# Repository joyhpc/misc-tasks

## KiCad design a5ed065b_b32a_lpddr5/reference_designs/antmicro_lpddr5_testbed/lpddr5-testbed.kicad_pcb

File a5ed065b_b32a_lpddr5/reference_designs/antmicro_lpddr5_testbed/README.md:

# LPDDR5 Testbed

Copyright (c) 2023-2025 [Antmicro](https://www.antmicro.com)

## Overview

This project contains open hardware design files for an experimental test module in a mechanical form of SO-DIMM DDR5. 

The module includes a standard 315-ball WFBGA (12.4mm × 15.0mm × 0.8mm, Ø0.42 SMD) LPDDR5 RAM footprint break-routed in the SO-DIMM edge connector. 
The design files were prepared in KiCad 9.x. 

Please note that this board is not electrically compatible with off-the-shelf hot platforms accepting SO-DIMM DDR5 memory modules. 
It is compatible with [this](https://github.com/antmicro/sodimm-ddr5-tester) test platform.

## Project structure

The main project directory contains KiCad PCB project files, a LICENSE and README. 
The remaining files are stored in the following directories:

* `img` - contains graphics for this README
* `doc` - contains PDF schematic

## Licensing

This project is published under the [Apache-2.0](LICENSE) license.

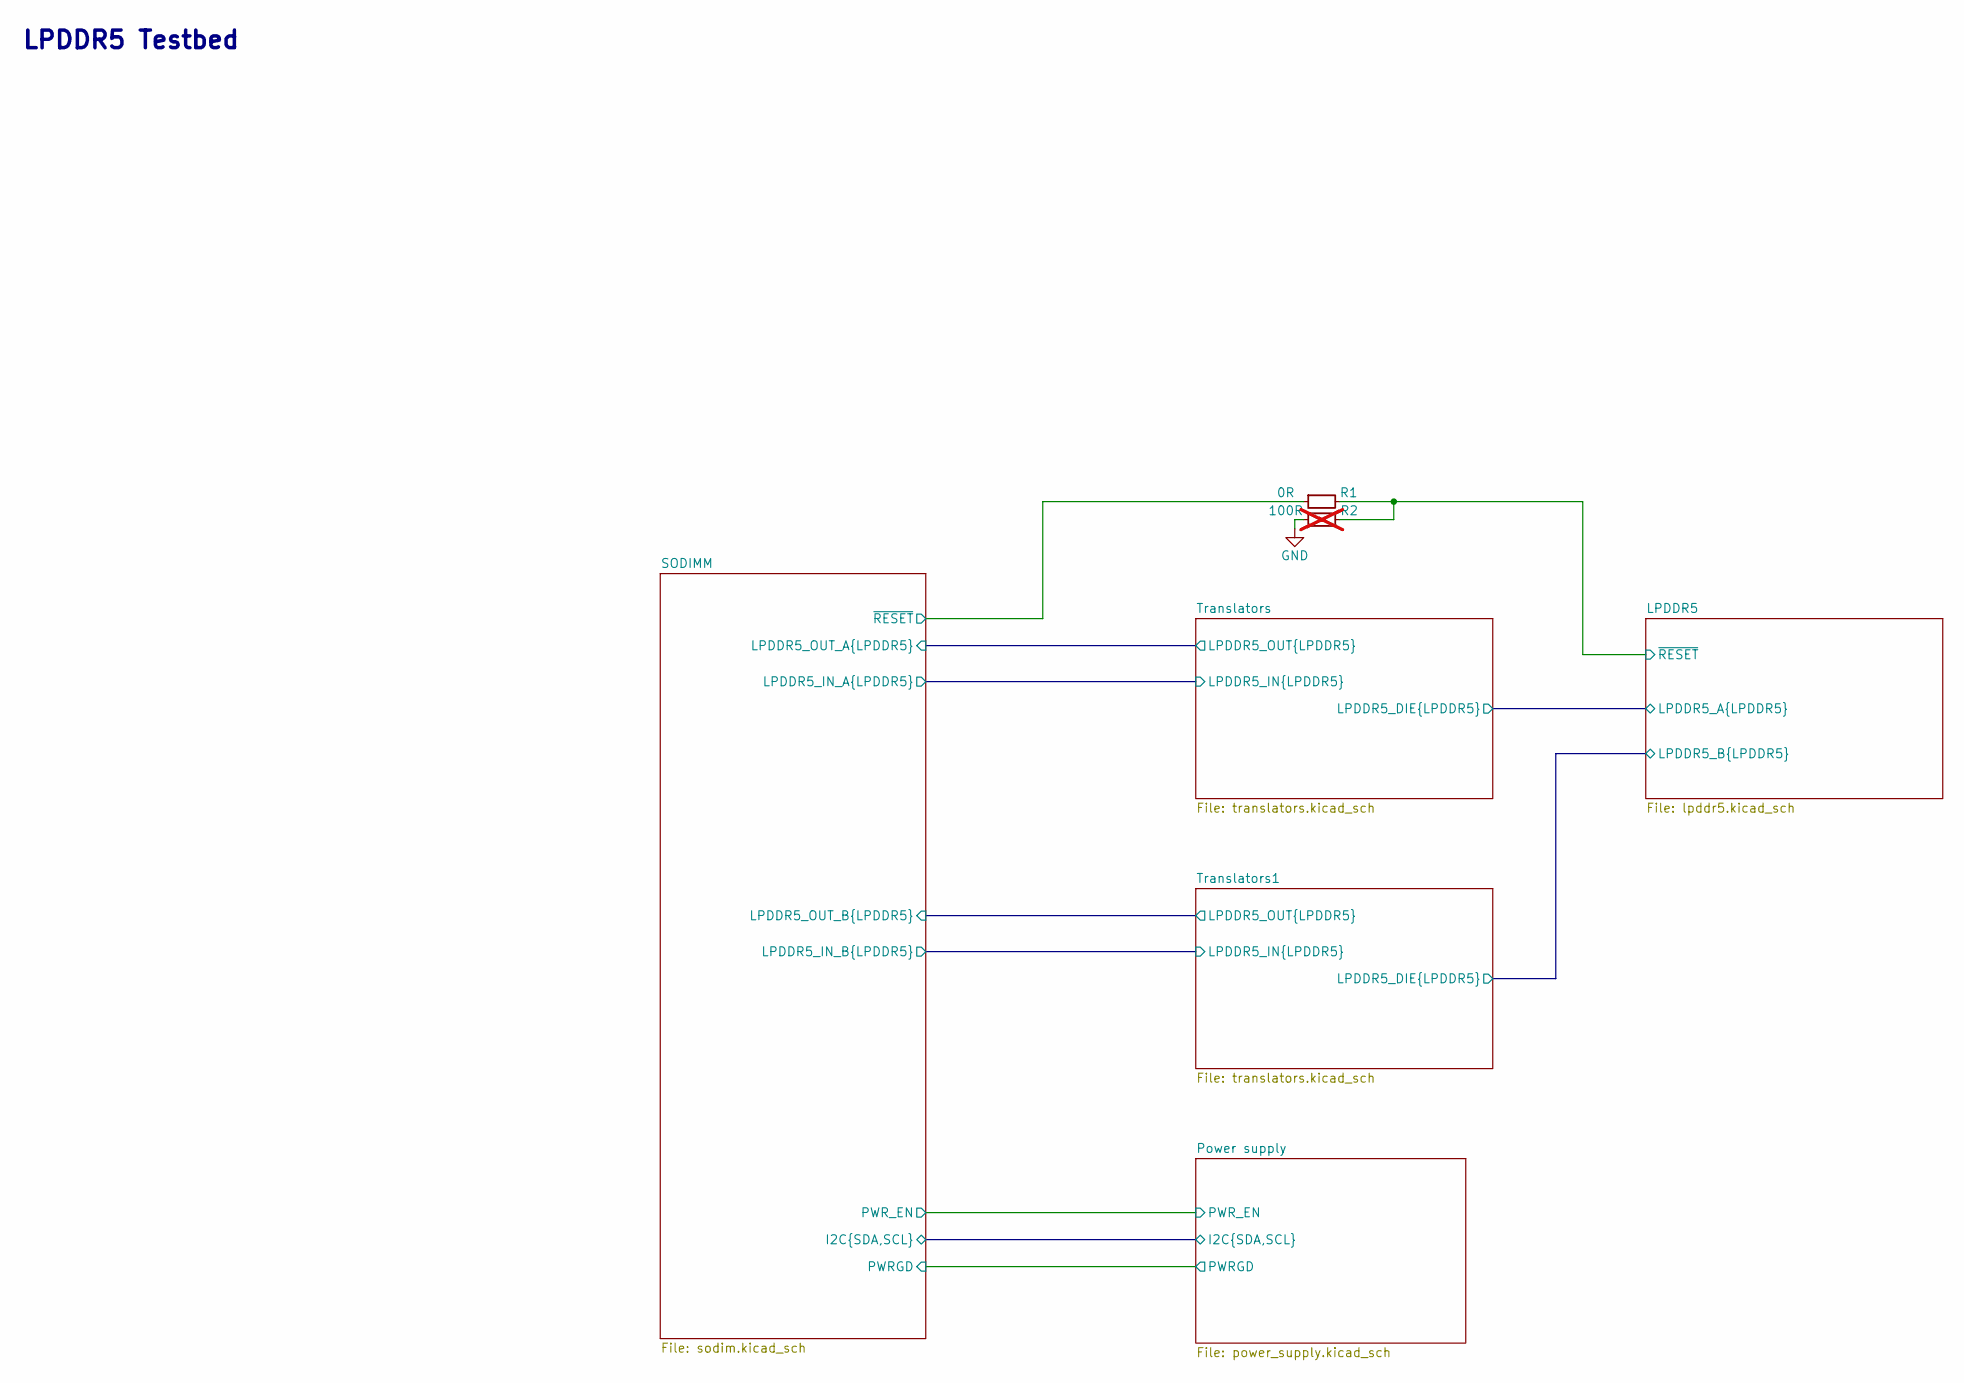
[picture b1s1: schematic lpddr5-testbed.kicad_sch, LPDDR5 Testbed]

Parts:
R1: R_0R_0402; R_0402_1005Metric; MPN ERJ2GE0R00X
R2: R_100R_0402; R_0402_1005Metric; Tolerance 1%; MPN CR0402-FX-1000GLF; not fitted

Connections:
/LPDDR5/~RESET: R1.2, R2.2; also elsewhere on the board
/SODIMM/~RESET: R1.1; also elsewhere on the board
GND: R2.1; also elsewhere on the board

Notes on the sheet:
LPDDR5 Testbed

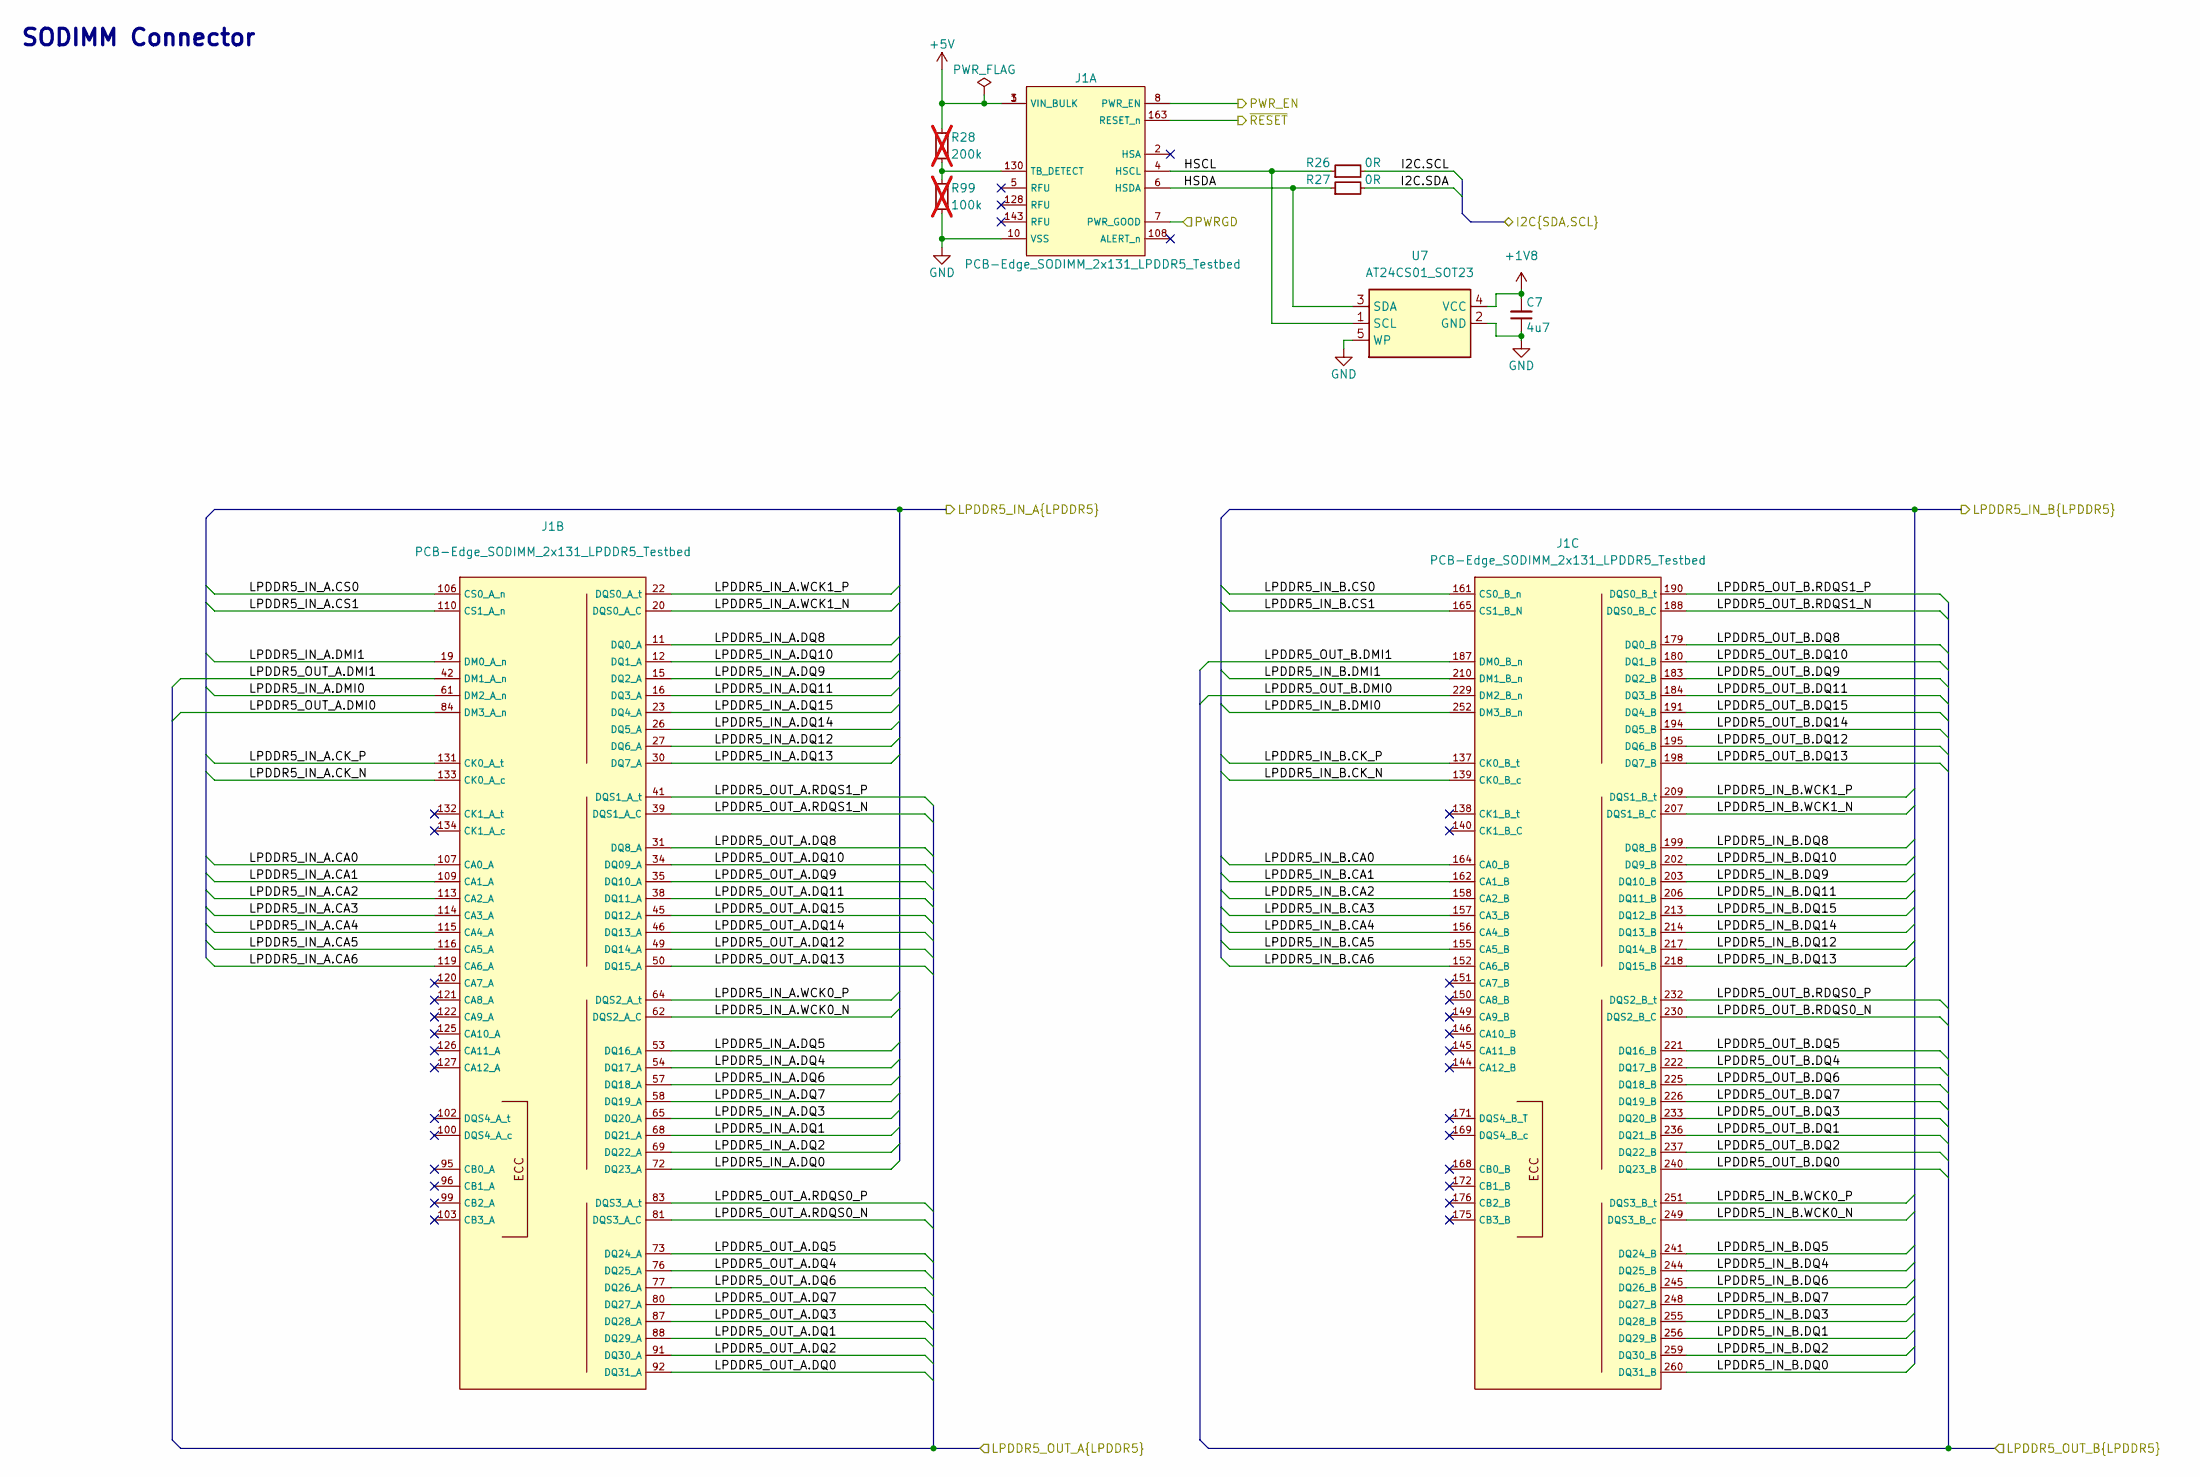
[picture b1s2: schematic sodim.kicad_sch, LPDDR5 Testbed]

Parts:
C7: C_4u7_0402; C_0402_1005Metric; MPN GRM155R61A475MEAAD
J1: PCB-Edge_SODIMM_2x131_LPDDR5_Testbed; Edge_Conn_Bus_DDR5_SODIMM
R26, R27: R_0R_0402; R_0402_1005Metric; MPN ERJ2GE0R00X
R28: R_200k_0402; R_0402_1005Metric; Tolerance 1%; MPN CR0402-FX-2003GLF; not fitted
R99: R_100k_0402; R_0402_1005Metric; Tolerance 1%; MPN CR0402-FX-1003GLF; not fitted
U7: AT24CS01_SOT23; SOT-23-5; MPN AT24CS01-ST

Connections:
+1V8: C7.2, U7.4 (VCC); also elsewhere on the board
+5V: J1.1 (VIN_BULK), J1.3 (VIN_BULK), R28.1; also elsewhere on the board
/LPDDR5/LPDDR5_A.DMI0: J1.84 (DM3_A_n); also elsewhere on the board
/LPDDR5/LPDDR5_A.DMI1: J1.42 (DM1_A_n); also elsewhere on the board
/LPDDR5/LPDDR5_A.DQ0: J1.92 (DQ31_A); also elsewhere on the board
/LPDDR5/LPDDR5_A.DQ1: J1.88 (DQ29_A); also elsewhere on the board
/LPDDR5/LPDDR5_A.DQ2: J1.91 (DQ30_A); also elsewhere on the board
/LPDDR5/LPDDR5_A.DQ3: J1.87 (DQ28_A); also elsewhere on the board
/LPDDR5/LPDDR5_A.DQ4: J1.76 (DQ25_A); also elsewhere on the board
/LPDDR5/LPDDR5_A.DQ5: J1.73 (DQ24_A); also elsewhere on the board
/LPDDR5/LPDDR5_A.DQ6: J1.77 (DQ26_A); also elsewhere on the board
/LPDDR5/LPDDR5_A.DQ7: J1.80 (DQ27_A); also elsewhere on the board
/LPDDR5/LPDDR5_A.DQ8: J1.31 (DQ8_A); also elsewhere on the board
/LPDDR5/LPDDR5_A.DQ9: J1.35 (DQ10_A); also elsewhere on the board
/LPDDR5/LPDDR5_A.DQ10: J1.34 (DQ09_A); also elsewhere on the board
/LPDDR5/LPDDR5_A.DQ11: J1.38 (DQ11_A); also elsewhere on the board
/LPDDR5/LPDDR5_A.DQ12: J1.49 (DQ14_A); also elsewhere on the board
/LPDDR5/LPDDR5_A.DQ13: J1.50 (DQ15_A); also elsewhere on the board
/LPDDR5/LPDDR5_A.DQ14: J1.46 (DQ13_A); also elsewhere on the board
/LPDDR5/LPDDR5_A.DQ15: J1.45 (DQ12_A); also elsewhere on the board
/LPDDR5/LPDDR5_A.RDQS0_N: J1.81 (DQS3_A_C); also elsewhere on the board
/LPDDR5/LPDDR5_A.RDQS0_P: J1.83 (DQS3_A_t); also elsewhere on the board
/LPDDR5/LPDDR5_A.RDQS1_N: J1.39 (DQS1_A_C); also elsewhere on the board
/LPDDR5/LPDDR5_A.RDQS1_P: J1.41 (DQS1_A_t); also elsewhere on the board
/LPDDR5/LPDDR5_B.DMI0: J1.229 (DM2_B_n); also elsewhere on the board
/LPDDR5/LPDDR5_B.DMI1: J1.187 (DM0_B_n); also elsewhere on the board
/LPDDR5/LPDDR5_B.DQ0: J1.240 (DQ23_B); also elsewhere on the board
/LPDDR5/LPDDR5_B.DQ1: J1.236 (DQ21_B); also elsewhere on the board
/LPDDR5/LPDDR5_B.DQ2: J1.237 (DQ22_B); also elsewhere on the board
/LPDDR5/LPDDR5_B.DQ3: J1.233 (DQ20_B); also elsewhere on the board
/LPDDR5/LPDDR5_B.DQ4: J1.222 (DQ17_B); also elsewhere on the board
/LPDDR5/LPDDR5_B.DQ5: J1.221 (DQ16_B); also elsewhere on the board
/LPDDR5/LPDDR5_B.DQ6: J1.225 (DQ18_B); also elsewhere on the board
/LPDDR5/LPDDR5_B.DQ7: J1.226 (DQ19_B); also elsewhere on the board
/LPDDR5/LPDDR5_B.DQ8: J1.179 (DQ0_B); also elsewhere on the board
/LPDDR5/LPDDR5_B.DQ9: J1.183 (DQ2_B); also elsewhere on the board
/LPDDR5/LPDDR5_B.DQ10: J1.180 (DQ1_B); also elsewhere on the board
/LPDDR5/LPDDR5_B.DQ11: J1.184 (DQ3_B); also elsewhere on the board
/LPDDR5/LPDDR5_B.DQ12: J1.195 (DQ6_B); also elsewhere on the board
/LPDDR5/LPDDR5_B.DQ13: J1.198 (DQ7_B); also elsewhere on the board
/LPDDR5/LPDDR5_B.DQ14: J1.194 (DQ5_B); also elsewhere on the board
/LPDDR5/LPDDR5_B.DQ15: J1.191 (DQ4_B); also elsewhere on the board
/LPDDR5/LPDDR5_B.RDQS0_N: J1.230 (DQS2_B_C); also elsewhere on the board
/LPDDR5/LPDDR5_B.RDQS0_P: J1.232 (DQS2_B_t); also elsewhere on the board
/LPDDR5/LPDDR5_B.RDQS1_N: J1.188 (DQS0_B_C); also elsewhere on the board
/LPDDR5/LPDDR5_B.RDQS1_P: J1.190 (DQS0_B_t); also elsewhere on the board
/Power supply/I2C.SCL: R26.2; also elsewhere on the board
/Power supply/I2C.SDA: R27.2; also elsewhere on the board
/Power supply/PWRGD: J1.7 (PWR_GOOD); also elsewhere on the board
/Power supply/PWR_EN: J1.8 (PWR_EN); also elsewhere on the board
/SODIMM/HSCL: J1.4 (HSCL), R26.1, U7.1 (SCL)
/SODIMM/HSDA: J1.6 (HSDA), R27.1, U7.3 (SDA)
/SODIMM/LPDDR5_IN_A.CA0: J1.107 (CA0_A); also elsewhere on the board
/SODIMM/LPDDR5_IN_A.CA1: J1.109 (CA1_A); also elsewhere on the board
/SODIMM/LPDDR5_IN_A.CA2: J1.113 (CA2_A); also elsewhere on the board
/SODIMM/LPDDR5_IN_A.CA3: J1.114 (CA3_A); also elsewhere on the board
/SODIMM/LPDDR5_IN_A.CA4: J1.115 (CA4_A); also elsewhere on the board
/SODIMM/LPDDR5_IN_A.CA5: J1.116 (CA5_A); also elsewhere on the board
/SODIMM/LPDDR5_IN_A.CA6: J1.119 (CA6_A); also elsewhere on the board
/SODIMM/LPDDR5_IN_A.CK_N: J1.133 (CK0_A_c); also elsewhere on the board
/SODIMM/LPDDR5_IN_A.CK_P: J1.131 (CK0_A_t); also elsewhere on the board
/SODIMM/LPDDR5_IN_A.CS0: J1.106 (CS0_A_n); also elsewhere on the board
/SODIMM/LPDDR5_IN_A.CS1: J1.110 (CS1_A_n); also elsewhere on the board
/SODIMM/LPDDR5_IN_A.DMI0: J1.61 (DM2_A_n); also elsewhere on the board
/SODIMM/LPDDR5_IN_A.DMI1: J1.19 (DM0_A_n); also elsewhere on the board
/SODIMM/LPDDR5_IN_A.DQ0: J1.72 (DQ23_A); also elsewhere on the board
/SODIMM/LPDDR5_IN_A.DQ1: J1.68 (DQ21_A); also elsewhere on the board
/SODIMM/LPDDR5_IN_A.DQ2: J1.69 (DQ22_A); also elsewhere on the board
/SODIMM/LPDDR5_IN_A.DQ3: J1.65 (DQ20_A); also elsewhere on the board
/SODIMM/LPDDR5_IN_A.DQ4: J1.54 (DQ17_A); also elsewhere on the board
/SODIMM/LPDDR5_IN_A.DQ5: J1.53 (DQ16_A); also elsewhere on the board
/SODIMM/LPDDR5_IN_A.DQ6: J1.57 (DQ18_A); also elsewhere on the board
/SODIMM/LPDDR5_IN_A.DQ7: J1.58 (DQ19_A); also elsewhere on the board
/SODIMM/LPDDR5_IN_A.DQ8: J1.11 (DQ0_A); also elsewhere on the board
/SODIMM/LPDDR5_IN_A.DQ9: J1.15 (DQ2_A); also elsewhere on the board
/SODIMM/LPDDR5_IN_A.DQ10: J1.12 (DQ1_A); also elsewhere on the board
/SODIMM/LPDDR5_IN_A.DQ11: J1.16 (DQ3_A); also elsewhere on the board
/SODIMM/LPDDR5_IN_A.DQ12: J1.27 (DQ6_A); also elsewhere on the board
/SODIMM/LPDDR5_IN_A.DQ13: J1.30 (DQ7_A); also elsewhere on the board
/SODIMM/LPDDR5_IN_A.DQ14: J1.26 (DQ5_A); also elsewhere on the board
/SODIMM/LPDDR5_IN_A.DQ15: J1.23 (DQ4_A); also elsewhere on the board
/SODIMM/LPDDR5_IN_A.WCK0_N: J1.62 (DQS2_A_C); also elsewhere on the board
/SODIMM/LPDDR5_IN_A.WCK0_P: J1.64 (DQS2_A_t); also elsewhere on the board
/SODIMM/LPDDR5_IN_A.WCK1_N: J1.20 (DQS0_A_C); also elsewhere on the board
/SODIMM/LPDDR5_IN_A.WCK1_P: J1.22 (DQS0_A_t); also elsewhere on the board
/SODIMM/LPDDR5_IN_B.CA0: J1.164 (CA0_B); also elsewhere on the board
/SODIMM/LPDDR5_IN_B.CA1: J1.162 (CA1_B); also elsewhere on the board
/SODIMM/LPDDR5_IN_B.CA2: J1.158 (CA2_B); also elsewhere on the board
/SODIMM/LPDDR5_IN_B.CA3: J1.157 (CA3_B); also elsewhere on the board
/SODIMM/LPDDR5_IN_B.CA4: J1.156 (CA4_B); also elsewhere on the board
/SODIMM/LPDDR5_IN_B.CA5: J1.155 (CA5_B); also elsewhere on the board
/SODIMM/LPDDR5_IN_B.CA6: J1.152 (CA6_B); also elsewhere on the board
/SODIMM/LPDDR5_IN_B.CK_N: J1.139 (CK0_B_c); also elsewhere on the board
/SODIMM/LPDDR5_IN_B.CK_P: J1.137 (CK0_B_t); also elsewhere on the board
/SODIMM/LPDDR5_IN_B.CS0: J1.161 (CS0_B_n); also elsewhere on the board
/SODIMM/LPDDR5_IN_B.CS1: J1.165 (CS1_B_N); also elsewhere on the board
/SODIMM/LPDDR5_IN_B.DMI0: J1.252 (DM3_B_n); also elsewhere on the board
/SODIMM/LPDDR5_IN_B.DMI1: J1.210 (DM1_B_n); also elsewhere on the board
/SODIMM/LPDDR5_IN_B.DQ0: J1.260 (DQ31_B); also elsewhere on the board
/SODIMM/LPDDR5_IN_B.DQ1: J1.256 (DQ29_B); also elsewhere on the board
/SODIMM/LPDDR5_IN_B.DQ2: J1.259 (DQ30_B); also elsewhere on the board
/SODIMM/LPDDR5_IN_B.DQ3: J1.255 (DQ28_B); also elsewhere on the board
/SODIMM/LPDDR5_IN_B.DQ4: J1.244 (DQ25_B); also elsewhere on the board
/SODIMM/LPDDR5_IN_B.DQ5: J1.241 (DQ24_B); also elsewhere on the board
/SODIMM/LPDDR5_IN_B.DQ6: J1.245 (DQ26_B); also elsewhere on the board
/SODIMM/LPDDR5_IN_B.DQ7: J1.248 (DQ27_B); also elsewhere on the board
/SODIMM/LPDDR5_IN_B.DQ8: J1.199 (DQ8_B); also elsewhere on the board
/SODIMM/LPDDR5_IN_B.DQ9: J1.203 (DQ10_B); also elsewhere on the board
/SODIMM/LPDDR5_IN_B.DQ10: J1.202 (DQ9_B); also elsewhere on the board
/SODIMM/LPDDR5_IN_B.DQ11: J1.206 (DQ11_B); also elsewhere on the board
/SODIMM/LPDDR5_IN_B.DQ12: J1.217 (DQ14_B); also elsewhere on the board
/SODIMM/LPDDR5_IN_B.DQ13: J1.218 (DQ15_B); also elsewhere on the board
/SODIMM/LPDDR5_IN_B.DQ14: J1.214 (DQ13_B); also elsewhere on the board
/SODIMM/LPDDR5_IN_B.DQ15: J1.213 (DQ12_B); also elsewhere on the board
/SODIMM/LPDDR5_IN_B.WCK0_N: J1.249 (DQS3_B_c); also elsewhere on the board
/SODIMM/LPDDR5_IN_B.WCK0_P: J1.251 (DQS3_B_t); also elsewhere on the board
/SODIMM/LPDDR5_IN_B.WCK1_N: J1.207 (DQS1_B_C); also elsewhere on the board
/SODIMM/LPDDR5_IN_B.WCK1_P: J1.209 (DQS1_B_t); also elsewhere on the board
/SODIMM/~RESET: J1.163 (RESET_n); also elsewhere on the board
GND: C7.1, J1.9 (VSS), J1.10 (VSS), J1.13 (VSS), J1.14 (VSS), J1.17 (VSS), J1.18 (VSS), J1.21 (VSS), J1.24 (VSS), J1.25 (VSS), J1.28 (VSS), J1.29 (VSS), J1.32 (VSS), J1.33 (VSS), J1.36 (VSS), J1.37 (VSS), J1.40 (VSS), J1.43 (VSS), J1.44 (VSS), J1.47 (VSS), J1.48 (VSS), J1.51 (VSS), J1.52 (VSS), J1.55 (VSS), J1.56 (VSS), J1.59 (VSS), J1.60 (VSS), J1.63 (VSS), J1.66 (VSS), J1.67 (VSS), J1.70 (VSS), J1.71 (VSS), J1.74 (VSS), J1.75 (VSS), J1.78 (VSS), J1.79 (VSS), J1.82 (VSS), J1.85 (VSS), J1.86 (VSS), J1.89 (VSS), J1.90 (VSS), J1.93 (VSS), J1.94 (VSS), J1.97 (VSS), J1.98 (VSS), J1.101 (VSS), J1.104 (VSS), J1.105 (VSS), J1.111 (VSS), J1.112 (VSS), J1.117 (VSS), J1.118 (VSS), J1.123 (VSS), J1.124 (VSS), J1.129 (VSS), J1.135 (VSS), J1.136 (VSS), J1.141 (VSS), J1.142 (VSS), J1.147 (VSS), J1.148 (VSS), J1.153 (VSS), J1.154 (VSS), J1.159 (VSS), J1.160 (VSS), J1.166 (VSS), J1.167 (VSS), J1.170 (VSS), J1.173 (VSS), J1.174 (VSS), J1.177 (VSS), J1.178 (VSS), J1.181 (VSS), J1.182 (VSS), J1.185 (VSS), J1.186 (VSS), J1.189 (VSS), J1.192 (VSS), J1.193 (VSS), J1.196 (VSS), J1.197 (VSS), J1.200 (VSS), J1.201 (VSS), J1.204 (VSS), J1.205 (VSS), J1.208 (VSS), J1.211 (VSS), J1.212 (VSS), J1.215 (VSS), J1.216 (VSS), J1.219 (VSS), J1.220 (VSS), J1.223 (VSS), J1.224 (VSS), J1.227 (VSS), J1.228 (VSS), J1.231 (VSS), J1.234 (VSS), J1.235 (VSS), J1.238 (VSS), J1.239 (VSS), J1.242 (VSS), J1.243 (VSS), J1.246 (VSS), J1.247 (VSS), J1.250 (VSS), J1.253 (VSS), J1.254 (VSS), J1.257 (VSS), J1.258 (VSS), J1.261 (VSS), J1.262 (VSS), R99.2, U7.2 (GND), U7.5 (WP); also elsewhere on the board
unnamed: J1.130 (TB_DETECT), R28.2, R99.1

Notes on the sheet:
SODIMM Connector

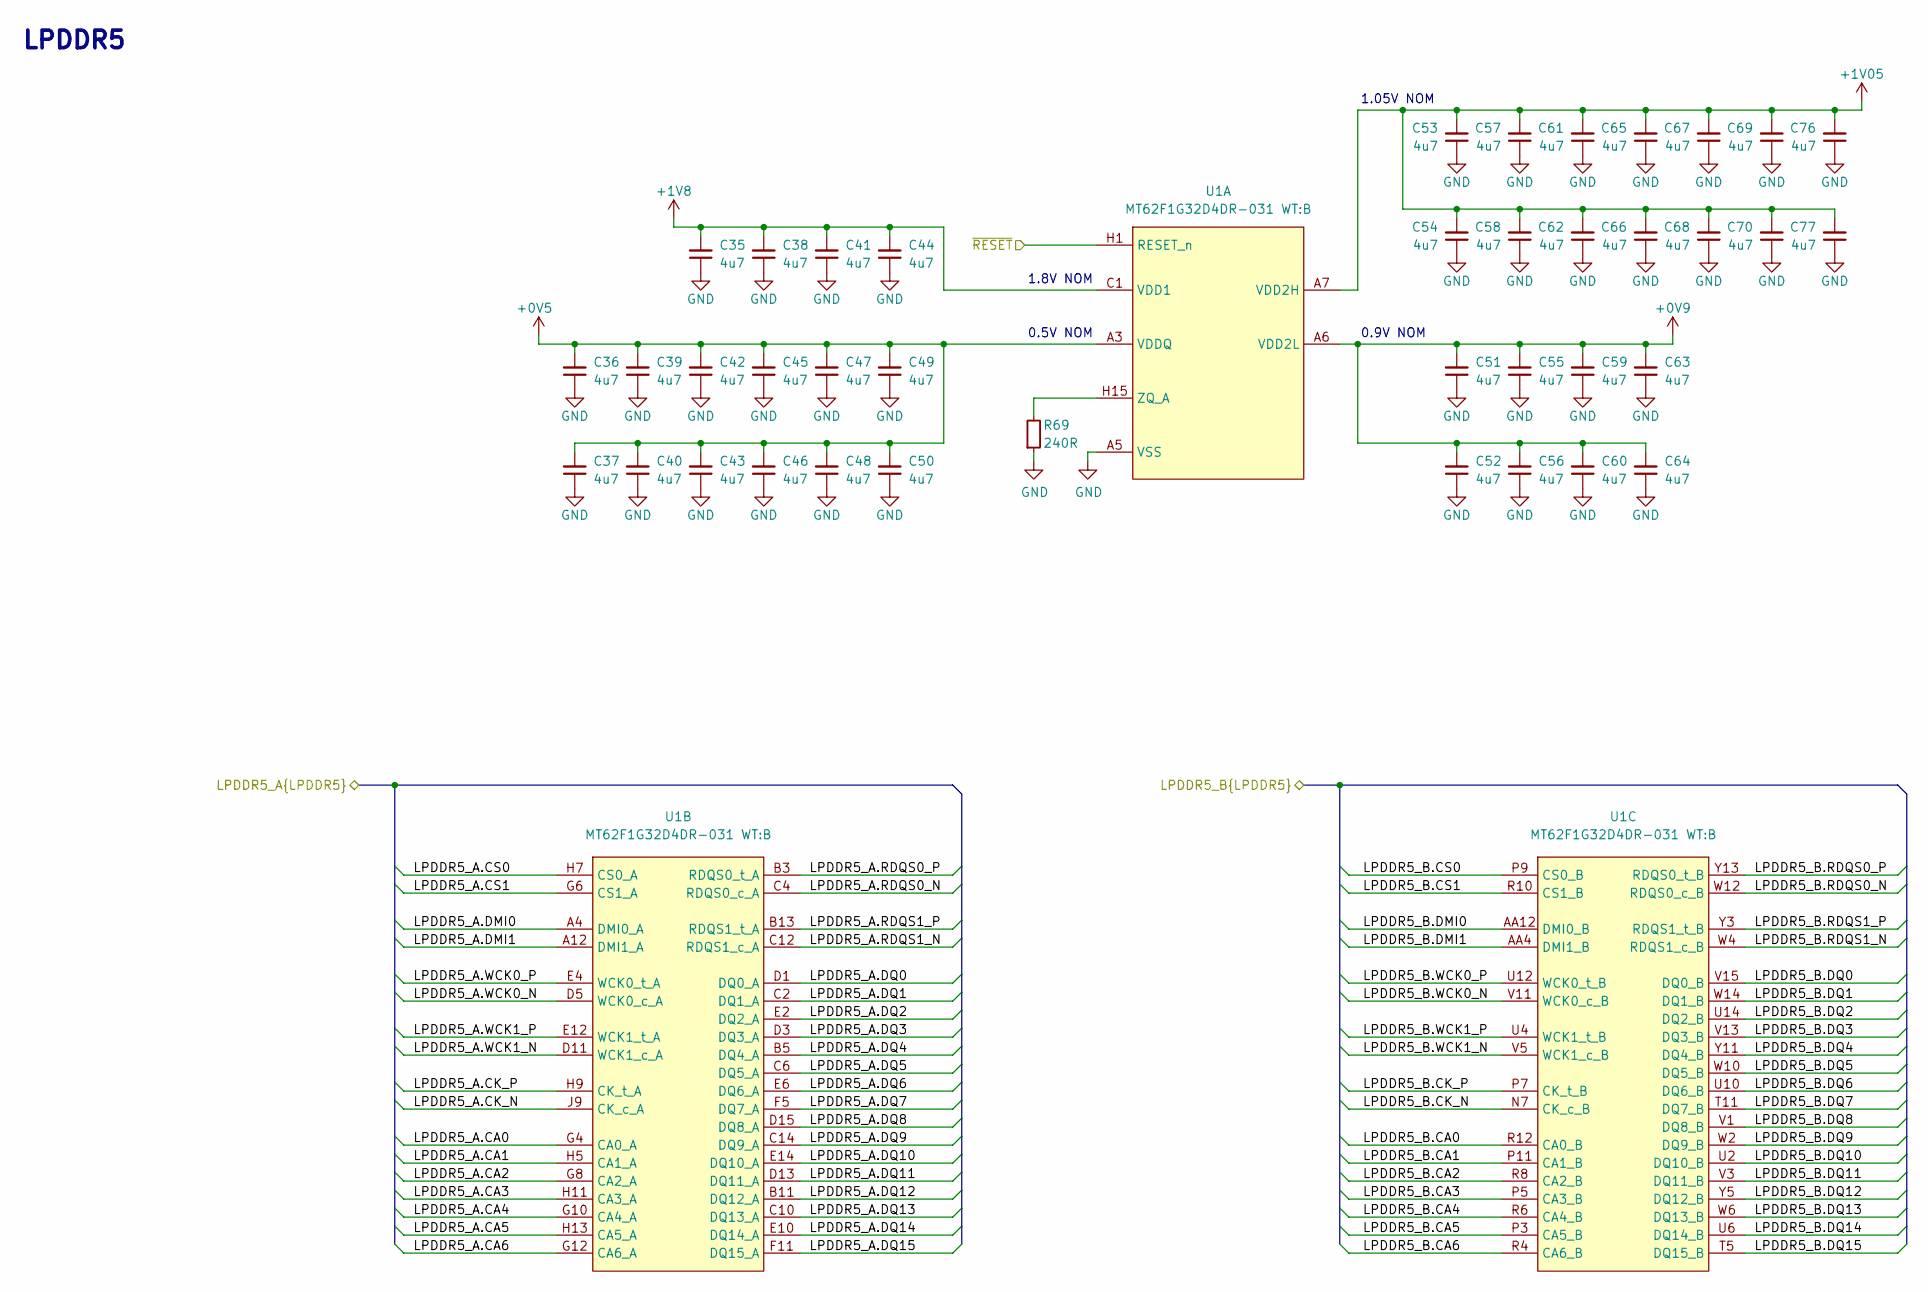
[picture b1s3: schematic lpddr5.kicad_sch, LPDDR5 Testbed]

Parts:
C35, C36, C37, C38, C39, C40, C41, C42, C43, C44, C45, C46, C47, C48, C49, C50, C51, C52, C53, C54, C55, C56, C57, C58, C59, C60, C61, C62, C63, C64, C65, C66, C67, C68, C69, C70, C76, C77: C_4u7_0402; C_0402_1005Metric; MPN GRM155R61A475MEAAD
R69: R_240R_0402; R_0402_1005Metric; Tolerance 1%; MPN CR0402-FX-2400GLF
U1: MT62F1G32D4DR-031; BGA-315_12.4x15mm_Layout15x21_P0.8x0.7mm; MPN MT62F1G32D4DR-031 WT:B

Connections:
+0V5: C36.2, C37.2, C39.2, C40.2, C42.2, C43.2, C45.2, C46.2, C47.2, C48.2, C49.2, C50.2, U1.A3 (VDDQ), U1.A13 (VDDQ), U1.AA3 (VDDQ), U1.AA13 (VDDQ), U1.B2 (VDDQ), U1.B14 (VDDQ), U1.C3 (VDDQ), U1.C13 (VDDQ), U1.D4 (VDDQ), U1.D12 (VDDQ), U1.E5 (VDDQ), U1.E11 (VDDQ), U1.F1 (VDDQ), U1.F3 (VDDQ), U1.F4 (VDDQ), U1.F12 (VDDQ), U1.F13 (VDDQ), U1.F15 (VDDQ), U1.G1 (VDDQ), U1.G2 (VDDQ), U1.G14 (VDDQ), U1.G15 (VDDQ), U1.R1 (VDDQ), U1.R2 (VDDQ), U1.R14 (VDDQ), U1.R15 (VDDQ), U1.T1 (VDDQ), U1.T3 (VDDQ), U1.T4 (VDDQ), U1.T12 (VDDQ), U1.T13 (VDDQ), U1.T15 (VDDQ), U1.U5 (VDDQ), U1.U11 (VDDQ), U1.V4 (VDDQ), U1.V12 (VDDQ), U1.W3 (VDDQ), U1.W13 (VDDQ), U1.Y2 (VDDQ), U1.Y14 (VDDQ); also elsewhere on the board
+0V9: C51.2, C52.2, C55.2, C56.2, C59.2, C60.2, C63.2, C64.2, U1.A6 (VDD2L), U1.A10 (VDD2L), U1.AA6 (VDD2L), U1.AA10 (VDD2L), U1.B6 (VDD2L), U1.B10 (VDD2L), U1.H2 (VDD2L), U1.H14 (VDD2L), U1.J2 (VDD2L), U1.J14 (VDD2L), U1.N2 (VDD2L), U1.N14 (VDD2L), U1.P2 (VDD2L), U1.P14 (VDD2L), U1.Y6 (VDD2L), U1.Y10 (VDD2L); also elsewhere on the board
+1V05: C53.2, C54.2, C57.2, C58.2, C61.2, C62.2, C65.2, C66.2, C67.2, C68.2, C69.2, C70.2, C76.2, C77.2, U1.A7 (VDD2H), U1.A8 (VDD2H), U1.A9 (VDD2H), U1.AA7 (VDD2H), U1.AA8 (VDD2H), U1.AA9 (VDD2H), U1.B7 (VDD2H), U1.B9 (VDD2H), U1.C7 (VDD2H), U1.C9 (VDD2H), U1.D8 (VDD2H), U1.E7 (VDD2H), U1.E9 (VDD2H), U1.F6 (VDD2H), U1.F7 (VDD2H), U1.F9 (VDD2H), U1.F10 (VDD2H), U1.J5 (VDD2H), U1.J11 (VDD2H), U1.K1 (VDD2H), U1.K2 (VDD2H), U1.K3 (VDD2H), U1.K4 (VDD2H), U1.K5 (VDD2H), U1.K6 (VDD2H), U1.K10 (VDD2H), U1.K11 (VDD2H), U1.K12 (VDD2H), U1.K13 (VDD2H), U1.K14 (VDD2H), U1.K15 (VDD2H), U1.L6 (VDD2H), U1.L7 (VDD2H), U1.L8 (VDD2H), U1.L9 (VDD2H), U1.L10 (VDD2H), U1.M1 (VDD2H), U1.M2 (VDD2H), U1.M3 (VDD2H), U1.M4 (VDD2H), U1.M5 (VDD2H), U1.M6 (VDD2H), U1.M10 (VDD2H), U1.M11 (VDD2H), U1.M12 (VDD2H), U1.M13 (VDD2H), U1.M14 (VDD2H), U1.M15 (VDD2H), U1.N5 (VDD2H), U1.N11 (VDD2H), U1.T6 (VDD2H), U1.T7 (VDD2H), U1.T9 (VDD2H), U1.T10 (VDD2H), U1.U7 (VDD2H), U1.U9 (VDD2H), U1.V8 (VDD2H), U1.W7 (VDD2H), U1.W9 (VDD2H), U1.Y7 (VDD2H), U1.Y9 (VDD2H); also elsewhere on the board
+1V8: C35.2, C38.2, C41.2, C44.2, U1.C1 (VDD1), U1.C15 (VDD1), U1.W1 (VDD1), U1.W15 (VDD1); also elsewhere on the board
/LPDDR5/LPDDR5_A.CA0: U1.G4 (CA0_A); also elsewhere on the board
/LPDDR5/LPDDR5_A.CA1: U1.H5 (CA1_A); also elsewhere on the board
/LPDDR5/LPDDR5_A.CA2: U1.G8 (CA2_A); also elsewhere on the board
/LPDDR5/LPDDR5_A.CA3: U1.H11 (CA3_A); also elsewhere on the board
/LPDDR5/LPDDR5_A.CA4: U1.G10 (CA4_A); also elsewhere on the board
/LPDDR5/LPDDR5_A.CA5: U1.H13 (CA5_A); also elsewhere on the board
/LPDDR5/LPDDR5_A.CA6: U1.G12 (CA6_A); also elsewhere on the board
/LPDDR5/LPDDR5_A.CK_N: U1.J9 (CK_c_A); also elsewhere on the board
/LPDDR5/LPDDR5_A.CK_P: U1.H9 (CK_t_A); also elsewhere on the board
/LPDDR5/LPDDR5_A.CS0: U1.H7 (CS0_A); also elsewhere on the board
/LPDDR5/LPDDR5_A.CS1: U1.G6 (CS1_A); also elsewhere on the board
/LPDDR5/LPDDR5_A.DMI0: U1.A4 (DMI0_A); also elsewhere on the board
/LPDDR5/LPDDR5_A.DMI1: U1.A12 (DMI1_A); also elsewhere on the board
/LPDDR5/LPDDR5_A.DQ0: U1.D1 (DQ0_A); also elsewhere on the board
/LPDDR5/LPDDR5_A.DQ1: U1.C2 (DQ1_A); also elsewhere on the board
/LPDDR5/LPDDR5_A.DQ2: U1.E2 (DQ2_A); also elsewhere on the board
/LPDDR5/LPDDR5_A.DQ3: U1.D3 (DQ3_A); also elsewhere on the board
/LPDDR5/LPDDR5_A.DQ4: U1.B5 (DQ4_A); also elsewhere on the board
/LPDDR5/LPDDR5_A.DQ5: U1.C6 (DQ5_A); also elsewhere on the board
/LPDDR5/LPDDR5_A.DQ6: U1.E6 (DQ6_A); also elsewhere on the board
/LPDDR5/LPDDR5_A.DQ7: U1.F5 (DQ7_A); also elsewhere on the board
/LPDDR5/LPDDR5_A.DQ8: U1.D15 (DQ8_A); also elsewhere on the board
/LPDDR5/LPDDR5_A.DQ9: U1.C14 (DQ9_A); also elsewhere on the board
/LPDDR5/LPDDR5_A.DQ10: U1.E14 (DQ10_A); also elsewhere on the board
/LPDDR5/LPDDR5_A.DQ11: U1.D13 (DQ11_A); also elsewhere on the board
/LPDDR5/LPDDR5_A.DQ12: U1.B11 (DQ12_A); also elsewhere on the board
/LPDDR5/LPDDR5_A.DQ13: U1.C10 (DQ13_A); also elsewhere on the board
/LPDDR5/LPDDR5_A.DQ14: U1.E10 (DQ14_A); also elsewhere on the board
/LPDDR5/LPDDR5_A.DQ15: U1.F11 (DQ15_A); also elsewhere on the board
/LPDDR5/LPDDR5_A.RDQS0_N: U1.C4 (RDQS0_c_A); also elsewhere on the board
/LPDDR5/LPDDR5_A.RDQS0_P: U1.B3 (RDQS0_t_A); also elsewhere on the board
/LPDDR5/LPDDR5_A.RDQS1_N: U1.C12 (RDQS1_c_A); also elsewhere on the board
/LPDDR5/LPDDR5_A.RDQS1_P: U1.B13 (RDQS1_t_A); also elsewhere on the board
/LPDDR5/LPDDR5_A.WCK0_N: U1.D5 (WCK0_c_A); also elsewhere on the board
/LPDDR5/LPDDR5_A.WCK0_P: U1.E4 (WCK0_t_A); also elsewhere on the board
/LPDDR5/LPDDR5_A.WCK1_N: U1.D11 (WCK1_c_A); also elsewhere on the board
/LPDDR5/LPDDR5_A.WCK1_P: U1.E12 (WCK1_t_A); also elsewhere on the board
/LPDDR5/LPDDR5_B.CA0: U1.R12 (CA0_B); also elsewhere on the board
/LPDDR5/LPDDR5_B.CA1: U1.P11 (CA1_B); also elsewhere on the board
/LPDDR5/LPDDR5_B.CA2: U1.R8 (CA2_B); also elsewhere on the board
/LPDDR5/LPDDR5_B.CA3: U1.P5 (CA3_B); also elsewhere on the board
/LPDDR5/LPDDR5_B.CA4: U1.R6 (CA4_B); also elsewhere on the board
/LPDDR5/LPDDR5_B.CA5: U1.P3 (CA5_B); also elsewhere on the board
/LPDDR5/LPDDR5_B.CA6: U1.R4 (CA6_B); also elsewhere on the board
/LPDDR5/LPDDR5_B.CK_N: U1.N7 (CK_c_B); also elsewhere on the board
/LPDDR5/LPDDR5_B.CK_P: U1.P7 (CK_t_B); also elsewhere on the board
/LPDDR5/LPDDR5_B.CS0: U1.P9 (CS0_B); also elsewhere on the board
/LPDDR5/LPDDR5_B.CS1: U1.R10 (CS1_B); also elsewhere on the board
/LPDDR5/LPDDR5_B.DMI0: U1.AA12 (DMI0_B); also elsewhere on the board
/LPDDR5/LPDDR5_B.DMI1: U1.AA4 (DMI1_B); also elsewhere on the board
/LPDDR5/LPDDR5_B.DQ0: U1.V15 (DQ0_B); also elsewhere on the board
/LPDDR5/LPDDR5_B.DQ1: U1.W14 (DQ1_B); also elsewhere on the board
/LPDDR5/LPDDR5_B.DQ2: U1.U14 (DQ2_B); also elsewhere on the board
/LPDDR5/LPDDR5_B.DQ3: U1.V13 (DQ3_B); also elsewhere on the board
/LPDDR5/LPDDR5_B.DQ4: U1.Y11 (DQ4_B); also elsewhere on the board
/LPDDR5/LPDDR5_B.DQ5: U1.W10 (DQ5_B); also elsewhere on the board
/LPDDR5/LPDDR5_B.DQ6: U1.U10 (DQ6_B); also elsewhere on the board
/LPDDR5/LPDDR5_B.DQ7: U1.T11 (DQ7_B); also elsewhere on the board
/LPDDR5/LPDDR5_B.DQ8: U1.V1 (DQ8_B); also elsewhere on the board
/LPDDR5/LPDDR5_B.DQ9: U1.W2 (DQ9_B); also elsewhere on the board
/LPDDR5/LPDDR5_B.DQ10: U1.U2 (DQ10_B); also elsewhere on the board
/LPDDR5/LPDDR5_B.DQ11: U1.V3 (DQ11_B); also elsewhere on the board
/LPDDR5/LPDDR5_B.DQ12: U1.Y5 (DQ12_B); also elsewhere on the board
/LPDDR5/LPDDR5_B.DQ13: U1.W6 (DQ13_B); also elsewhere on the board
/LPDDR5/LPDDR5_B.DQ14: U1.U6 (DQ14_B); also elsewhere on the board
/LPDDR5/LPDDR5_B.DQ15: U1.T5 (DQ15_B); also elsewhere on the board
/LPDDR5/LPDDR5_B.RDQS0_N: U1.W12 (RDQS0_c_B); also elsewhere on the board
/LPDDR5/LPDDR5_B.RDQS0_P: U1.Y13 (RDQS0_t_B); also elsewhere on the board
/LPDDR5/LPDDR5_B.RDQS1_N: U1.W4 (RDQS1_c_B); also elsewhere on the board
/LPDDR5/LPDDR5_B.RDQS1_P: U1.Y3 (RDQS1_t_B); also elsewhere on the board
/LPDDR5/LPDDR5_B.WCK0_N: U1.V11 (WCK0_c_B); also elsewhere on the board
/LPDDR5/LPDDR5_B.WCK0_P: U1.U12 (WCK0_t_B); also elsewhere on the board
/LPDDR5/LPDDR5_B.WCK1_N: U1.V5 (WCK1_c_B); also elsewhere on the board
/LPDDR5/LPDDR5_B.WCK1_P: U1.U4 (WCK1_t_B); also elsewhere on the board
/LPDDR5/~RESET: U1.H1 (RESET_n); also elsewhere on the board
GND: C35.1, C36.1, C37.1, C38.1, C39.1, C40.1, C41.1, C42.1, C43.1, C44.1, C45.1, C46.1, C47.1, C48.1, C49.1, C50.1, C51.1, C52.1, C53.1, C54.1, C55.1, C56.1, C57.1, C58.1, C59.1, C60.1, C61.1, C62.1, C63.1, C64.1, C65.1, C66.1, C67.1, C68.1, C69.1, C70.1, C76.1, C77.1, R69.1, U1.A5 (VSS), U1.A11 (VSS), U1.AA5 (VSS), U1.AA11 (VSS), U1.B4 (VSS), U1.B8 (VSS), U1.B12 (VSS), U1.C5 (VSS), U1.C8 (VSS), U1.C11 (VSS), U1.D2 (VSS), U1.D6 (VSS), U1.D7 (VSS), U1.D9 (VSS), U1.D10 (VSS), U1.D14 (VSS), U1.E1 (VSS), U1.E3 (VSS), U1.E8 (VSS), U1.E13 (VSS), U1.E15 (VSS), U1.F2 (VSS), U1.F8 (VSS), U1.F14 (VSS), U1.G3 (VSS), U1.G5 (VSS), U1.G7 (VSS), U1.G9 (VSS), U1.G11 (VSS), U1.G13 (VSS), U1.H3 (VSS), U1.H4 (VSS), U1.H6 (VSS), U1.H8 (VSS), U1.H10 (VSS), U1.H12 (VSS), U1.J1 (VSS), U1.J3 (VSS), U1.J7 (VSS), U1.J8 (VSS), U1.J10 (VSS), U1.J12 (VSS), U1.J13 (VSS), U1.J15 (VSS), U1.K7 (VSS), U1.K8 (VSS), U1.K9 (VSS), U1.L1 (VSS), U1.L2 (VSS), U1.L3 (VSS), U1.L4 (VSS), U1.L5 (VSS), U1.L11 (VSS), U1.L12 (VSS), U1.L13 (VSS), U1.L14 (VSS), U1.L15 (VSS), U1.M7 (VSS), U1.M8 (VSS), U1.M9 (VSS), U1.N1 (VSS), U1.N3 (VSS), U1.N4 (VSS), U1.N6 (VSS), U1.N8 (VSS), U1.N9 (VSS), U1.N10 (VSS), U1.N12 (VSS), U1.N13 (VSS), U1.N15 (VSS), U1.P4 (VSS), U1.P6 (VSS), U1.P8 (VSS), U1.P10 (VSS), U1.P12 (VSS), U1.P13 (VSS), U1.R3 (VSS), U1.R5 (VSS), U1.R7 (VSS), U1.R9 (VSS), U1.R11 (VSS), U1.R13 (VSS), U1.T2 (VSS), U1.T8 (VSS), U1.T14 (VSS), U1.U1 (VSS), U1.U3 (VSS), U1.U8 (VSS), U1.U13 (VSS), U1.U15 (VSS), U1.V2 (VSS), U1.V6 (VSS), U1.V7 (VSS), U1.V9 (VSS), U1.V10 (VSS), U1.V14 (VSS), U1.W5 (VSS), U1.W8 (VSS), U1.W11 (VSS), U1.Y4 (VSS), U1.Y8 (VSS), U1.Y12 (VSS); also elsewhere on the board
unnamed: R69.2, U1.H15 (ZQ_A)

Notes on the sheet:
0.5V NOM
0.9V NOM
1.05V NOM
LPDDR5
1.8V NOM

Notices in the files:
parts and their libraries:
License: Apache-2.0
